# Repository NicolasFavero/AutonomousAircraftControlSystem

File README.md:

# Sistema de Controle e Telemetria para Asa Autônoma

Este projeto é um **protótipo em desenvolvimento** de um sistema embarcado para uma **asa autônoma / aeromodelo experimental**, baseado em **ESP32-C3**.

O sistema realiza a aquisição de dados de sensores inerciais e ambientais, controla os servomotores das superfícies de comando e registra os dados de voo em um cartão microSD para análise posterior.

---

## Objetivo

Desenvolver uma plataforma embarcada capaz de:

- Adquirir dados de sensores inerciais;
- Medir pressão atmosférica e altitude;
- Medir velocidade do ar através de tubo de Pitot;
- Estimar a atitude da aeronave;
- Controlar superfícies móveis da aeronave;
- Registrar os dados de voo para análise posterior;
- Servir como base para futuras versões do sistema de navegação e telemetria.

---

## Funcionalidades

- Leitura de acelerômetro;
- Leitura de giroscópio;
- Leitura de magnetômetro;
- Estimativa de Pitch, Roll e Yaw;
- Medição de pressão atmosférica;
- Cálculo de altitude utilizando BMP280;
- Medição de velocidade do ar via tubo de Pitot;
- Controle de servomotores;
- Controle de:
  - Flaperon(Flap + Aileron);

- Registro automático dos dados em cartão microSD;
- Estrutura preparada para expansão futura.

---

## Status do Projeto

🚧 **Protótipo em desenvolvimento**

O hardware e o firmware encontram-se em constante evolução e podem sofrer alterações frequentes.

---

## Hardware Utilizado

- ESP32-C3;
- GY-91 (MPU9250 + BMP280);
- Tubo de Pitot;
- Módulo para cartão microSD;
- Servomotores.

---

## Tecnologias Utilizadas

- C / C++;
- Arduino Framework;
- Arduino IDE.

---

## Dependências

### Sensores

- MPU9250_asukiaaa — v1.5.13
- Adafruit BMP280 Library — v3.0.0

### Armazenamento

- SdFat — v2.3.0

### Core Arduino

- SPI
- Wire

### ESP32

- esp_adc_cal
- esp_task_wdt

---

## Ambiente de Desenvolvimento

- Arduino IDE 2.3.7
- Arduino Core for ESP32 v2.x
- Placa alvo: ESP32-C3

---

## Estrutura do Projeto

```text
Firmware/
└── Firmware.ino
```

---

## Aplicação

Projeto desenvolvido para fins educacionais e experimentais, integrando conhecimentos de:

- Programação embarcada;
- Eletrônica;
- Sensores inerciais;
- Aquisição de dados;
- Sistemas aeronáuticos;
- Controle de voo.

O projeto serve como base para o desenvolvimento de futuras versões do sistema de controle, navegação e telemetria da aeronave.

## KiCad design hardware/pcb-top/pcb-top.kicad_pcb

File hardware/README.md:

# Hardware

Esta pasta contém os arquivos de hardware do projeto, incluindo esquemáticos, layouts e demais arquivos relacionados às placas de circuito impresso (PCBs).

O sistema foi dividido em **duas PCBs empilháveis**, conectadas através de **headers macho e fêmea (2,54 mm)**. Essa arquitetura facilita a montagem, manutenção e futuras revisões do hardware, além de permitir uma melhor organização dos circuitos.

## PCB-Top

A **PCB-Top** concentra os circuitos de alimentação, armazenamento e navegação da aeronave, incluindo:

- Receptor GPS;
- Slot para cartão microSD;
- Conector da bateria;
- Conectores para servomotores;
- Conversor Buck (Step-Down);
- Capacitores de bulk para estabilização da alimentação;
- Distribuição das tensões de alimentação.

Também é nesta placa que ocorre a separação entre as linhas de alimentação de **3,3 V**, utilizando **ferrite beads** para isolar os diferentes domínios de alimentação, reduzindo a propagação de ruído entre os circuitos analógicos, digitais e de RF.

## PCB-Bottom

A **PCB-Bottom** concentra os circuitos responsáveis pelo processamento, sensoriamento e comunicação da aeronave, incluindo:

- ESP32-S3 SuperMini;
- IMU ICM-20948;
- BMP280;
- ADS1115;
- Módulo LoRa (RF96W ou módulos compatíveis da mesma família, como CC68);
- Conector para antena;
- Interface para tubo de Pitot.

A proximidade entre esses componentes reduz o comprimento das trilhas dos barramentos de comunicação e dos sinais de alta frequência, contribuindo para uma melhor integridade dos sinais.

## Interconexão

As duas placas são interligadas através de **headers macho e fêmea**, formando um conjunto compacto e removível.

Essa abordagem oferece diversas vantagens:

- Organização dos circuitos por função;
- Facilidade de montagem e manutenção;
- Possibilidade de substituir apenas uma das placas em futuras revisões;
- Redução da complexidade do roteamento;
- Melhor gerenciamento da distribuição de alimentação.

## Estrutura

```text
Hardware/
├── PCB-Top/
└── PCB-Bottom/
```

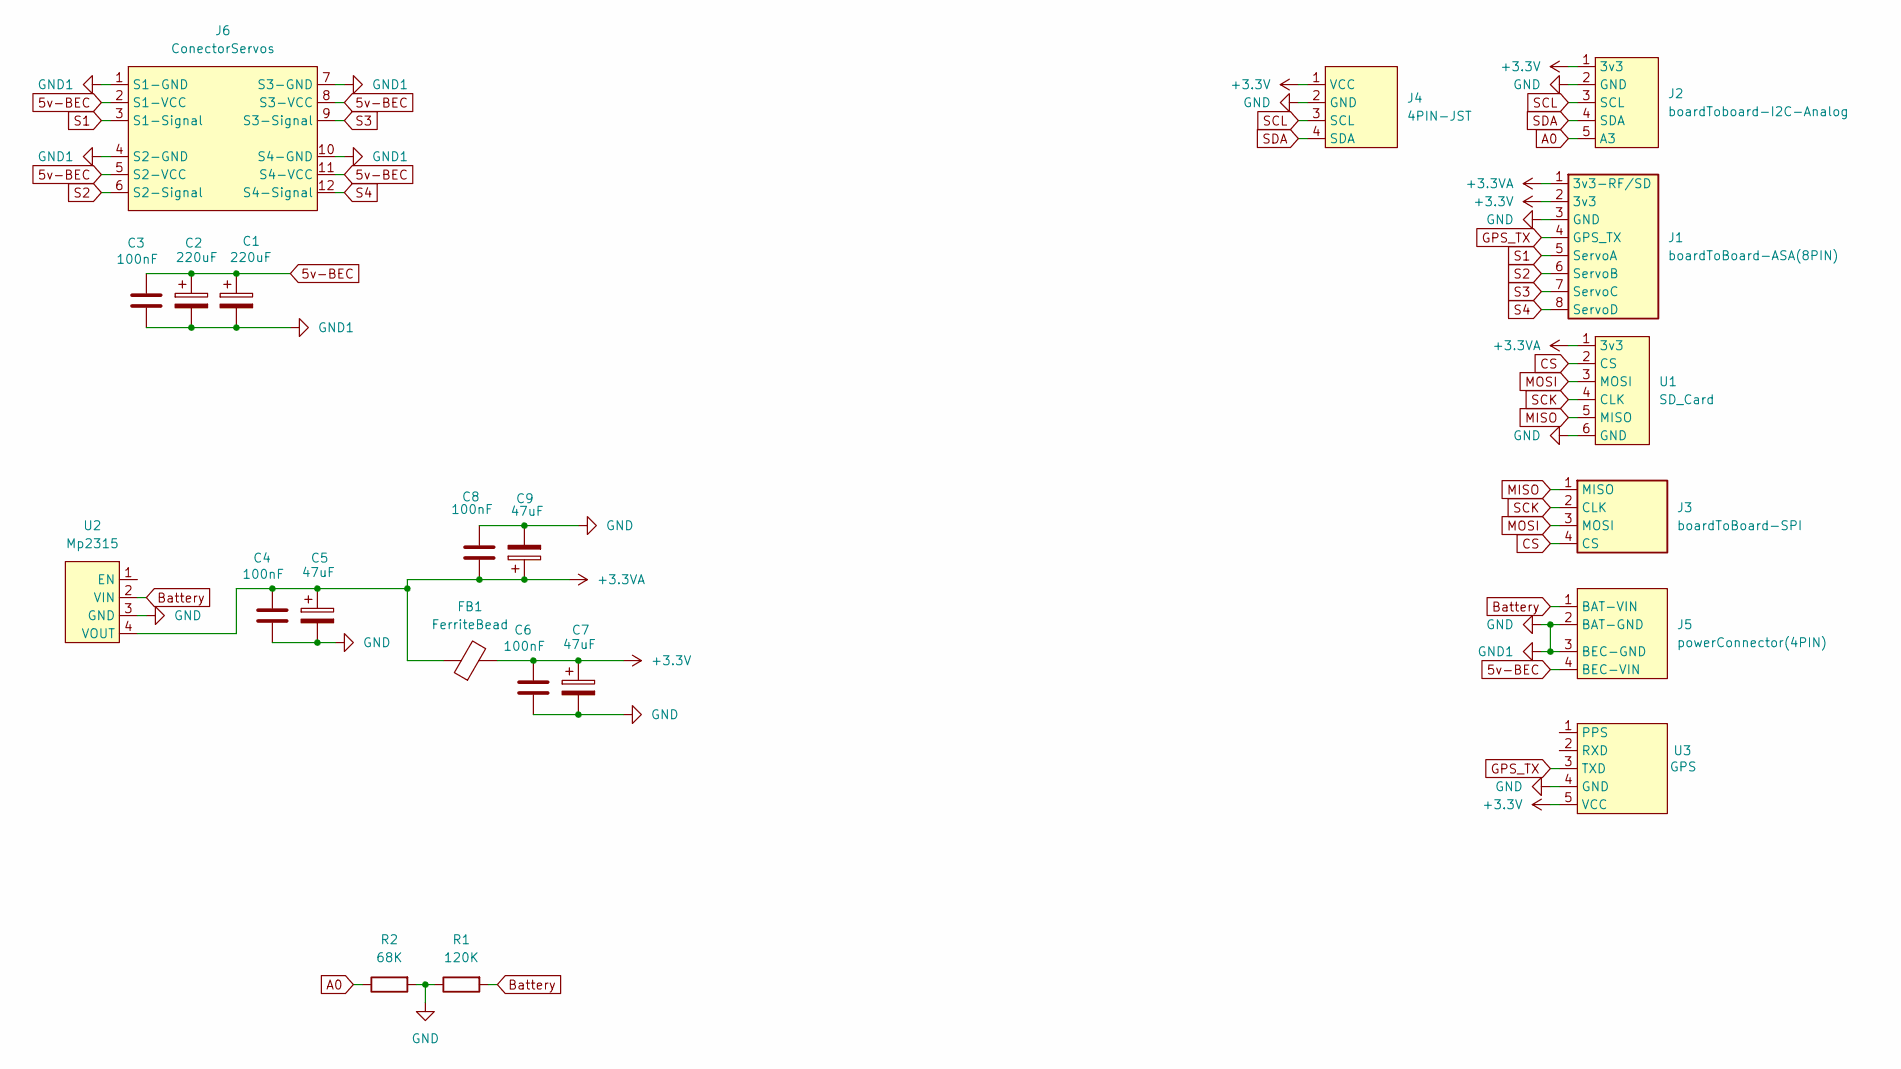
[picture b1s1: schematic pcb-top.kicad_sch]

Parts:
C1, C2: 220uF; CP_Radial_D6.3mm_P2.50mm
C3, C4, C6, C8: 100nF; C_Disc_D3.8mm_W2.6mm_P2.50mm
C5, C7, C9: 47uF; CP_Radial_D6.3mm_P2.50mm
FB1: FerriteBead; R_1206_3216Metric_Pad1.30x1.75mm_HandSolder
J1: boardToBoard-ASA(8PIN); PinSocket_1x08_P2.54mm_Vertical
J2: boardToboard-I2C-Analog; PinHeader_1x05_P2.54mm_Vertical
J3: boardToBoard-SPI; PinHeader_1x04_P2.54mm_Vertical
J4: 4PIN-JST; JST_XH_B4B-XH-A_1x04_P2.50mm_Vertical
J5: powerConnector(4PIN); ConnectorBaterry+BEC
J6: ConectorServos; 4Servos
R1: 120K; R_Axial_DIN0207_L6.3mm_D2.5mm_P7.62mm_Horizontal
R2: 68K; R_Axial_DIN0207_L6.3mm_D2.5mm_P7.62mm_Horizontal
U1: SD_Card
U2: Mp2315
U3: GPS

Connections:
5v-BEC: C1.1, C2.1, C3.1, J5.4 (BEC-VIN), J6.2 (S1-VCC), J6.5 (S2-VCC), J6.8 (S3-VCC), J6.11 (S4-VCC)
+3.3V: C6.1, C7.1, FB1.2, J1.2 (3v3), J2.1 (3v3), J4.1 (VCC), U3.5 (VCC)
+3.3VA: C4.1, C5.1, C8.1, C9.1, FB1.1, J1.1 (3v3-RF/SD), U1.1 (3v3), U2.4 (VOUT)
A0: J2.5 (A3), R2.1
Battery: J5.1 (BAT-VIN), R1.2, U2.2 (VIN)
CS: J3.4 (CS), U1.2 (CS)
GND: C1.2, C2.2, C3.2, C4.2, C5.2, C6.2, C7.2, C8.2, C9.2, J1.3 (GND), J2.2 (GND), J4.2 (GND), J5.2 (BAT-GND), J5.3 (BEC-GND), J6.1 (S1-GND), J6.4 (S2-GND), J6.7 (S3-GND), J6.10 (S4-GND), R1.1, R2.2, U1.6 (GND), U2.3 (GND), U3.4 (GND)
GPS_TX: J1.4 (GPS_TX), U3.3 (TXD)
MISO: J3.1 (MISO), U1.5 (MISO)
MOSI: J3.3 (MOSI), U1.3 (MOSI)
S1: J1.5 (ServoA), J6.3 (S1-Signal)
S2: J1.6 (ServoB), J6.6 (S2-Signal)
S3: J1.7 (ServoC), J6.9 (S3-Signal)
S4: J1.8 (ServoD), J6.12 (S4-Signal)
SCK: J3.2 (CLK), U1.4 (CLK)
SCL: J2.3 (SCL), J4.3 (SCL)
SDA: J2.4 (SDA), J4.4 (SDA)

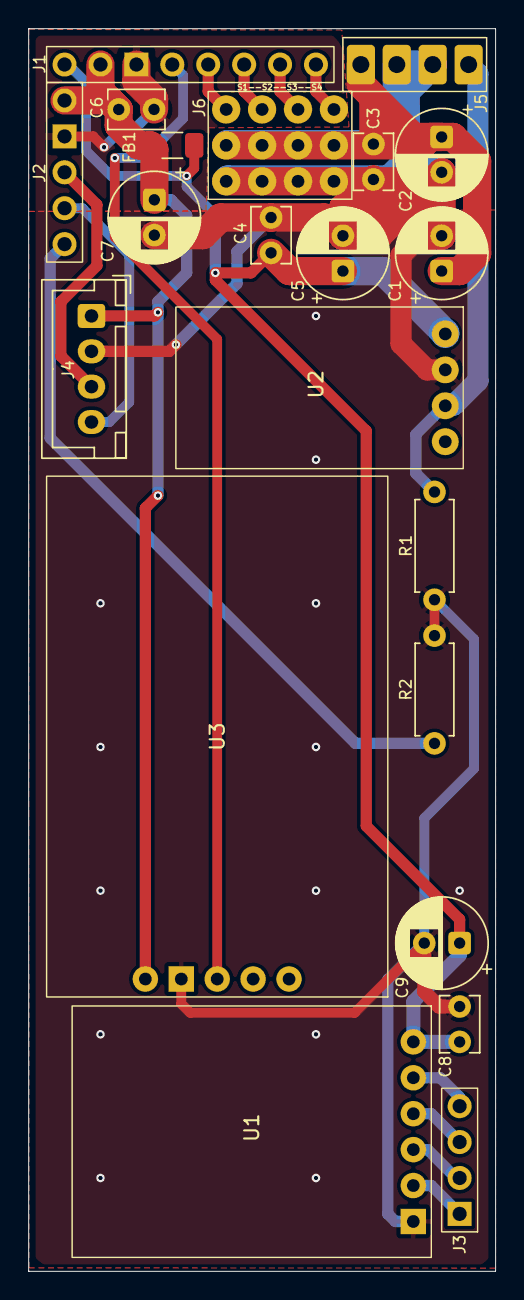
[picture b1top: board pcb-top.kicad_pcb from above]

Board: 2 copper layers, 33.0 x 87.9 mm, 21 parts (0 on the bottom side), 17 nets.

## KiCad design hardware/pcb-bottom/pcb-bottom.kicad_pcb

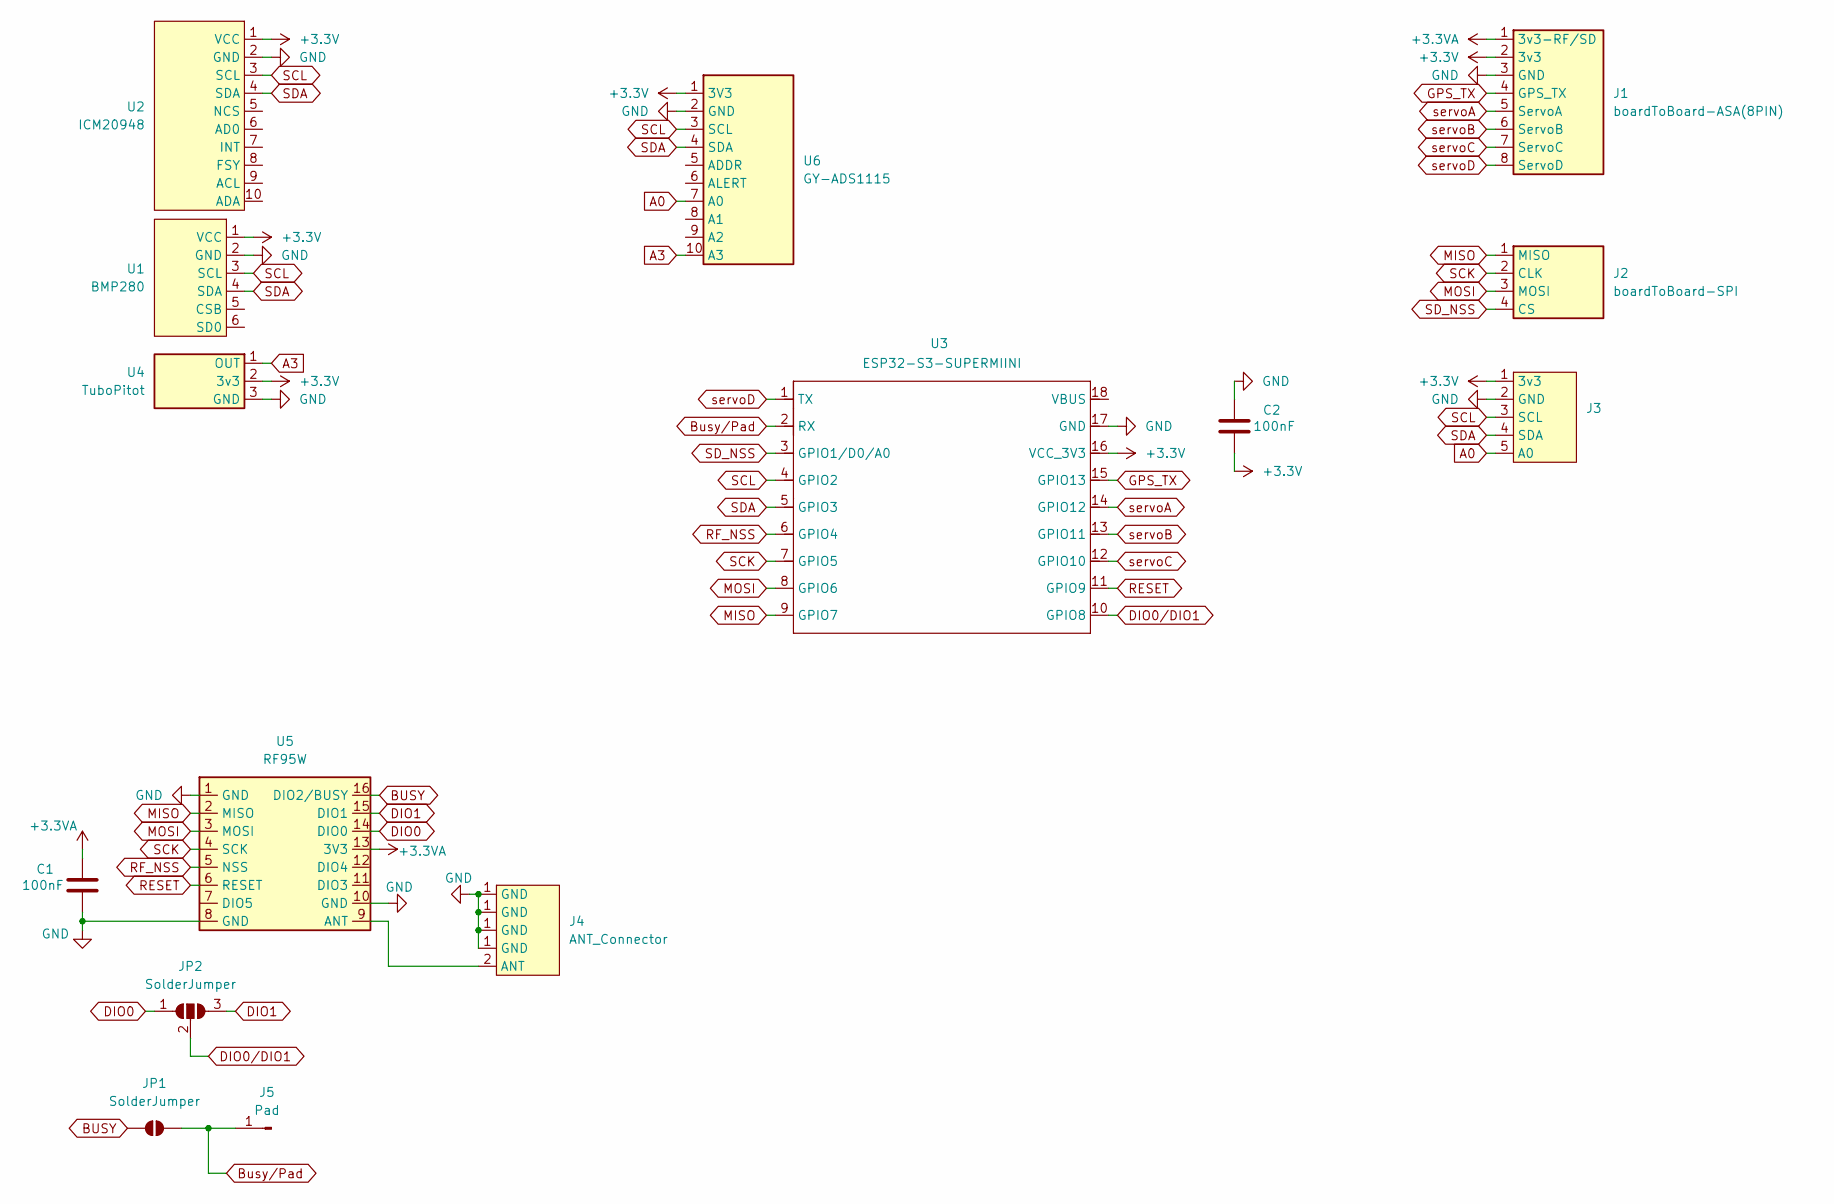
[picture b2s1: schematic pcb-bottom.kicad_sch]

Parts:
C1, C2: 100nF; C_Disc_D3.8mm_W2.6mm_P2.50mm
J1: boardToBoard-ASA(8PIN); PinHeader_1x08_P2.54mm_Vertical
J2: boardToBoard-SPI; PinHeader_1x04_P2.54mm_Vertical
J3: PinHeader_1x05_P2.54mm_Vertical
J4: ANT_Connector; conectorAntena2.54mm
J5: Pad; PinHeader_1x01_P2.54mm_Vertical
JP1: SolderJumper; SolderJumper-2_P1.3mm_Open_RoundedPad1.0x1.5mm
JP2: SolderJumper; SolderJumper-3_P1.3mm_Open_RoundedPad1.0x1.5mm
U1: BMP280
U2: ICM20948; ICM 20948
U3: ESP32-S3-SUPERMIINI; myEsp32-S3-Mini
U4: TuboPitot; tuboPitot
U5: RF95W; rf96w
U6: GY-ADS1115; ads1115

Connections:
+3.3V: C2.1, J1.2 (3v3), J3.1 (3v3), U1.1 (VCC), U2.1 (VCC), U3.16 (VCC_3V3), U4.2 (3v3), U6.1 (3V3)
+3.3VA: C1.2, J1.1 (3v3-RF/SD), U5.13 (3V3)
A0: J3.5 (A0), U6.7 (A0)
A3: U4.1 (OUT), U6.10 (A3)
BUSY: JP1.1 (A), U5.16 (DIO2/BUSY)
Busy/Pad: J5.1, JP1.2 (B), U3.2 (RX)
DIO0: JP2.1 (A), U5.14 (DIO0)
DIO0/DIO1: JP2.2 (C), U3.10 (GPIO8)
DIO1: JP2.3 (B), U5.15 (DIO1)
GND: C1.1, C2.2, J1.3 (GND), J3.2 (GND), J4.1 (GND), U1.2 (GND), U2.2 (GND), U3.17 (GND), U4.3 (GND), U5.1 (GND), U5.8 (GND), U5.10 (GND), U6.2 (GND)
GPS_TX: J1.4 (GPS_TX), U3.15 (GPIO13)
MISO: J2.1 (MISO), U3.9 (GPIO7), U5.2 (MISO)
MOSI: J2.3 (MOSI), U3.8 (GPIO6), U5.3 (MOSI)
unnamed: J4.2 (ANT), U5.9 (ANT)
RESET: U3.11 (GPIO9), U5.6 (RESET)
RF_NSS: U3.6 (GPIO4), U5.5 (NSS)
SCK: J2.2 (CLK), U3.7 (GPIO5), U5.4 (SCK)
SCL: J3.3 (SCL), U1.3 (SCL), U2.3 (SCL), U3.4 (GPIO2), U6.3 (SCL)
SDA: J3.4 (SDA), U1.4 (SDA), U2.4 (SDA), U3.5 (GPIO3), U6.4 (SDA)
SD_NSS: J2.4 (CS), U3.3 (GPIO1/D0/A0)
servoA: J1.5 (ServoA), U3.14 (GPIO12)
servoB: J1.6 (ServoB), U3.13 (GPIO11)
servoC: J1.7 (ServoC), U3.12 (GPIO10)
servoD: J1.8 (ServoD), U3.1 (TX)

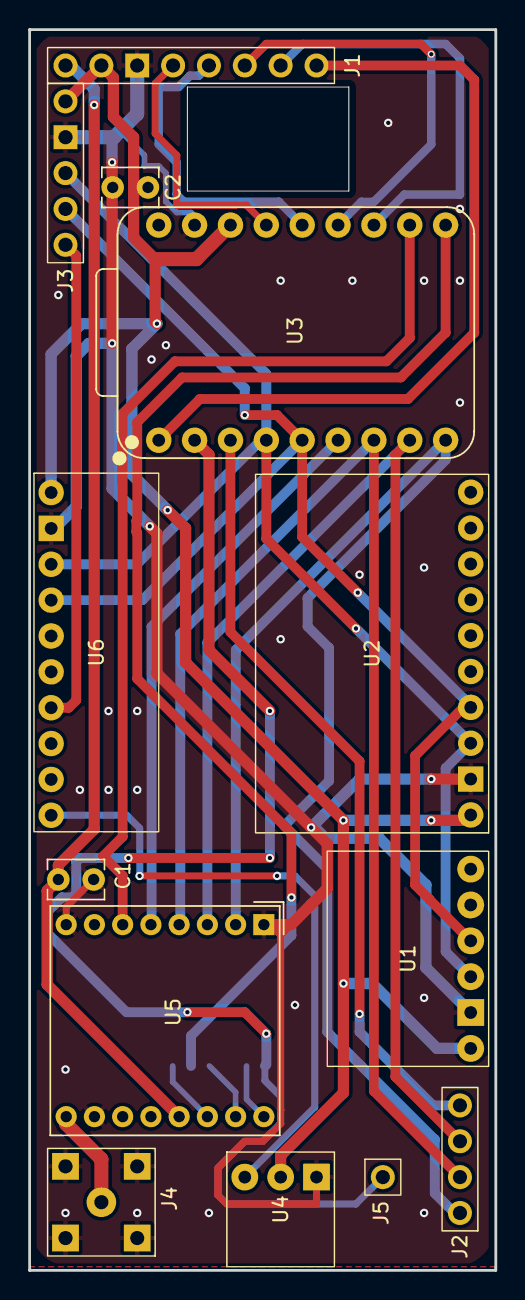
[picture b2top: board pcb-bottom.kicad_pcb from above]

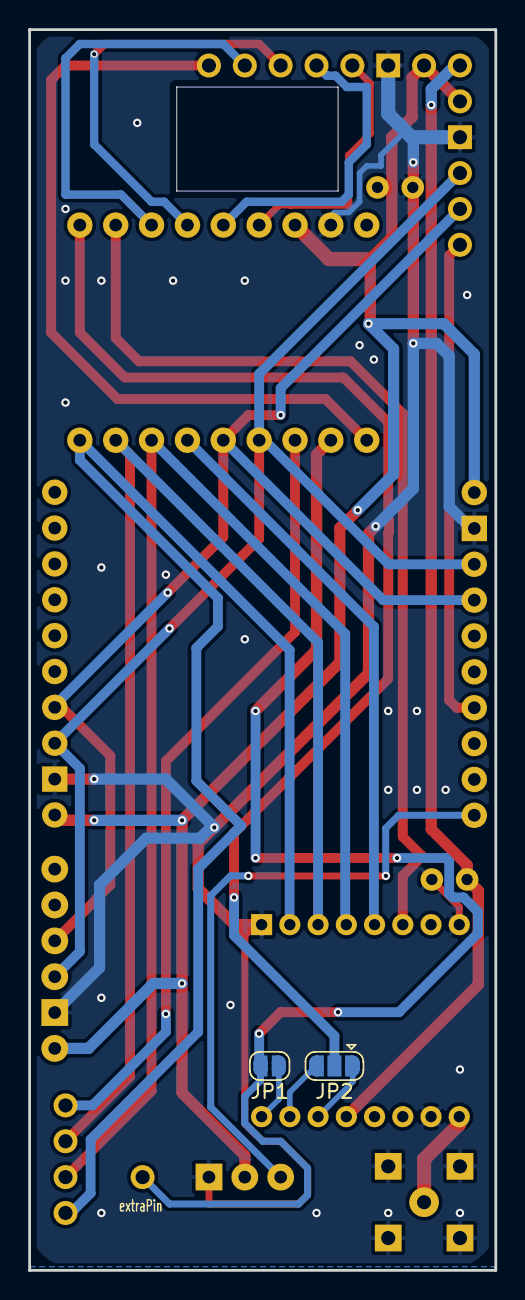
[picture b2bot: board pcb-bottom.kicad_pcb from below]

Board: 2 copper layers, 33.0 x 87.9 mm, 15 parts (2 on the bottom side), 24 nets.
